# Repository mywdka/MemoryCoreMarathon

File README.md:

# MemoryCoreMarathon
UNRAVEL THE CODE IV, Memory Core Marathon

# Weaving, Driving, Dreaming

Based on the Memory Core Shield from B. North and O. Nash.
Slight routing modifications done to the driver layout, silkscreen and Arduino API.

WdKA API for Unravel the code can be found in the code/ folder.

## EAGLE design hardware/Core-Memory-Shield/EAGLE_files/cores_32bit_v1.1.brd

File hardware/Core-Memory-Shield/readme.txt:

More details of this project can be found at:

    http://www.corememoryshield.com/

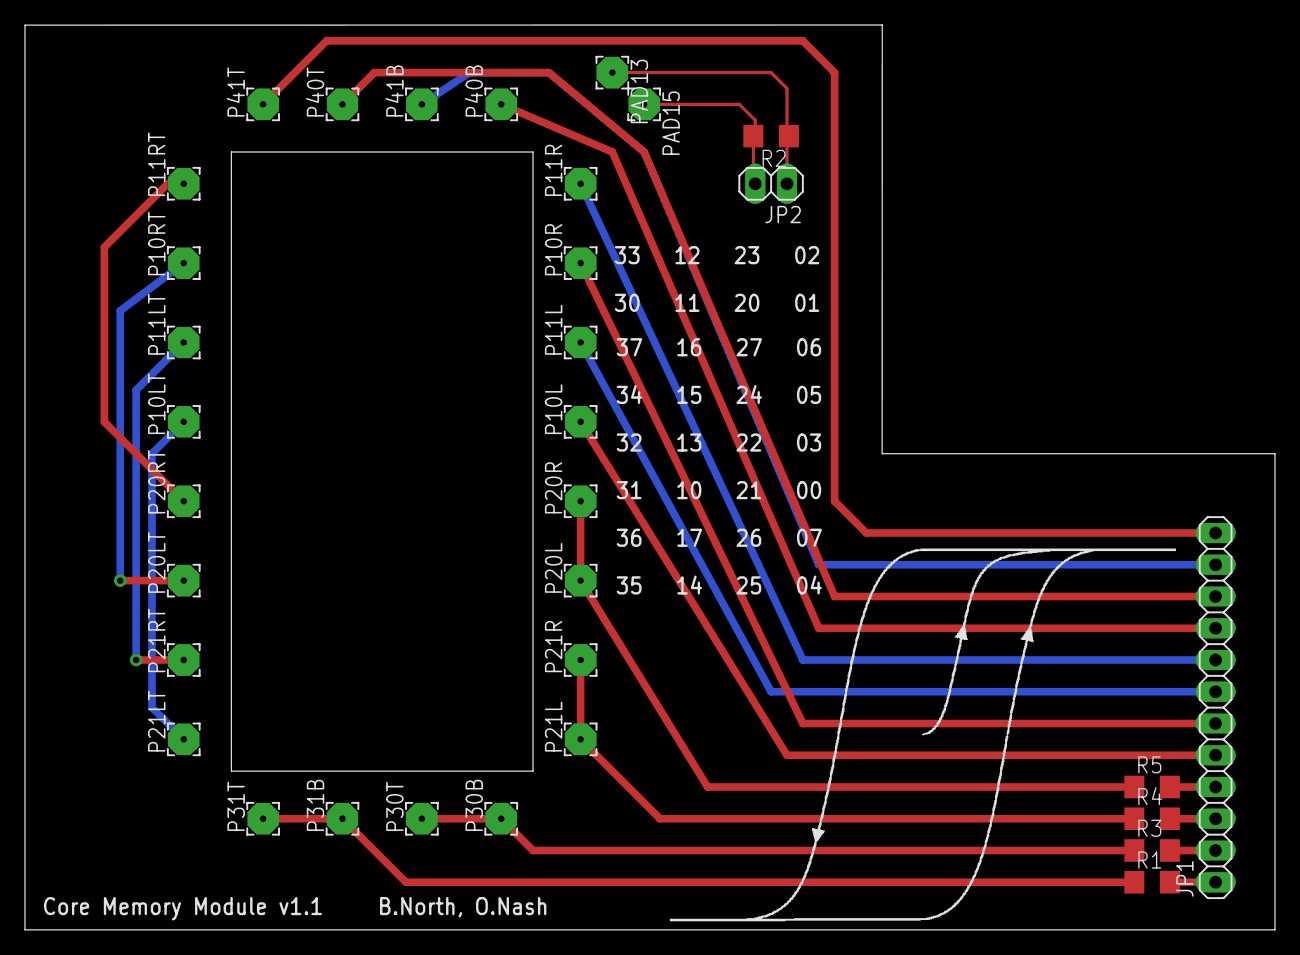
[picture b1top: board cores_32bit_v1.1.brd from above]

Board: 2 copper layers, 100.0 x 72.4 mm, 33 parts (0 on the bottom side), 22 nets.

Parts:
JP1: DRIVER BOARD; 1X12
JP2: SENSE; 1X02
P10L, P10LT, P10R, P10RT, P11L, P11LT, P11R, P11RT, P20L, P20LT, P20R, P20RT, P21L, P21LT, P21R, P21RT, P30B, P30T, P31B, P31T, P40B, P40T, P41B, P41T: WIREPAD2,54/1,1; 2,54/1,1
PAD13, PAD15: WIREPAD2,54/1,1; 2,54/1,1
R1, R3, R4, R5: 18; R1206
R2: 220; R1206

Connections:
D10A: JP1.5, P10L.1
D10B: JP1.6, P10R.1
D11A: JP1.7, P11L.1
D11B: JP1.8, P11R.1
D20: P20L.1, P20R.1, R5.1
D21: P21L.1, P21R.1, R4.1
D30: P30B.1, P30T.1, R3.1
D31: P31B.1, P31T.1, R1.1
D40A: JP1.9, P40B.1
D40B: JP1.10, P40T.1
D41A: JP1.11, P41B.1
D41B: JP1.12, P41T.1
unnamed: JP2.1, PAD13.1, R2.1
unnamed: JP2.2, PAD15.1, R2.2
unnamed: JP1.1, R1.2
unnamed: JP1.2, R3.2
unnamed: JP1.3, R4.2
unnamed: JP1.4, R5.2
unnamed: P10LT.1, P21LT.1
unnamed: P11LT.1, P21RT.1
unnamed: P10RT.1, P20LT.1
unnamed: P11RT.1, P20RT.1

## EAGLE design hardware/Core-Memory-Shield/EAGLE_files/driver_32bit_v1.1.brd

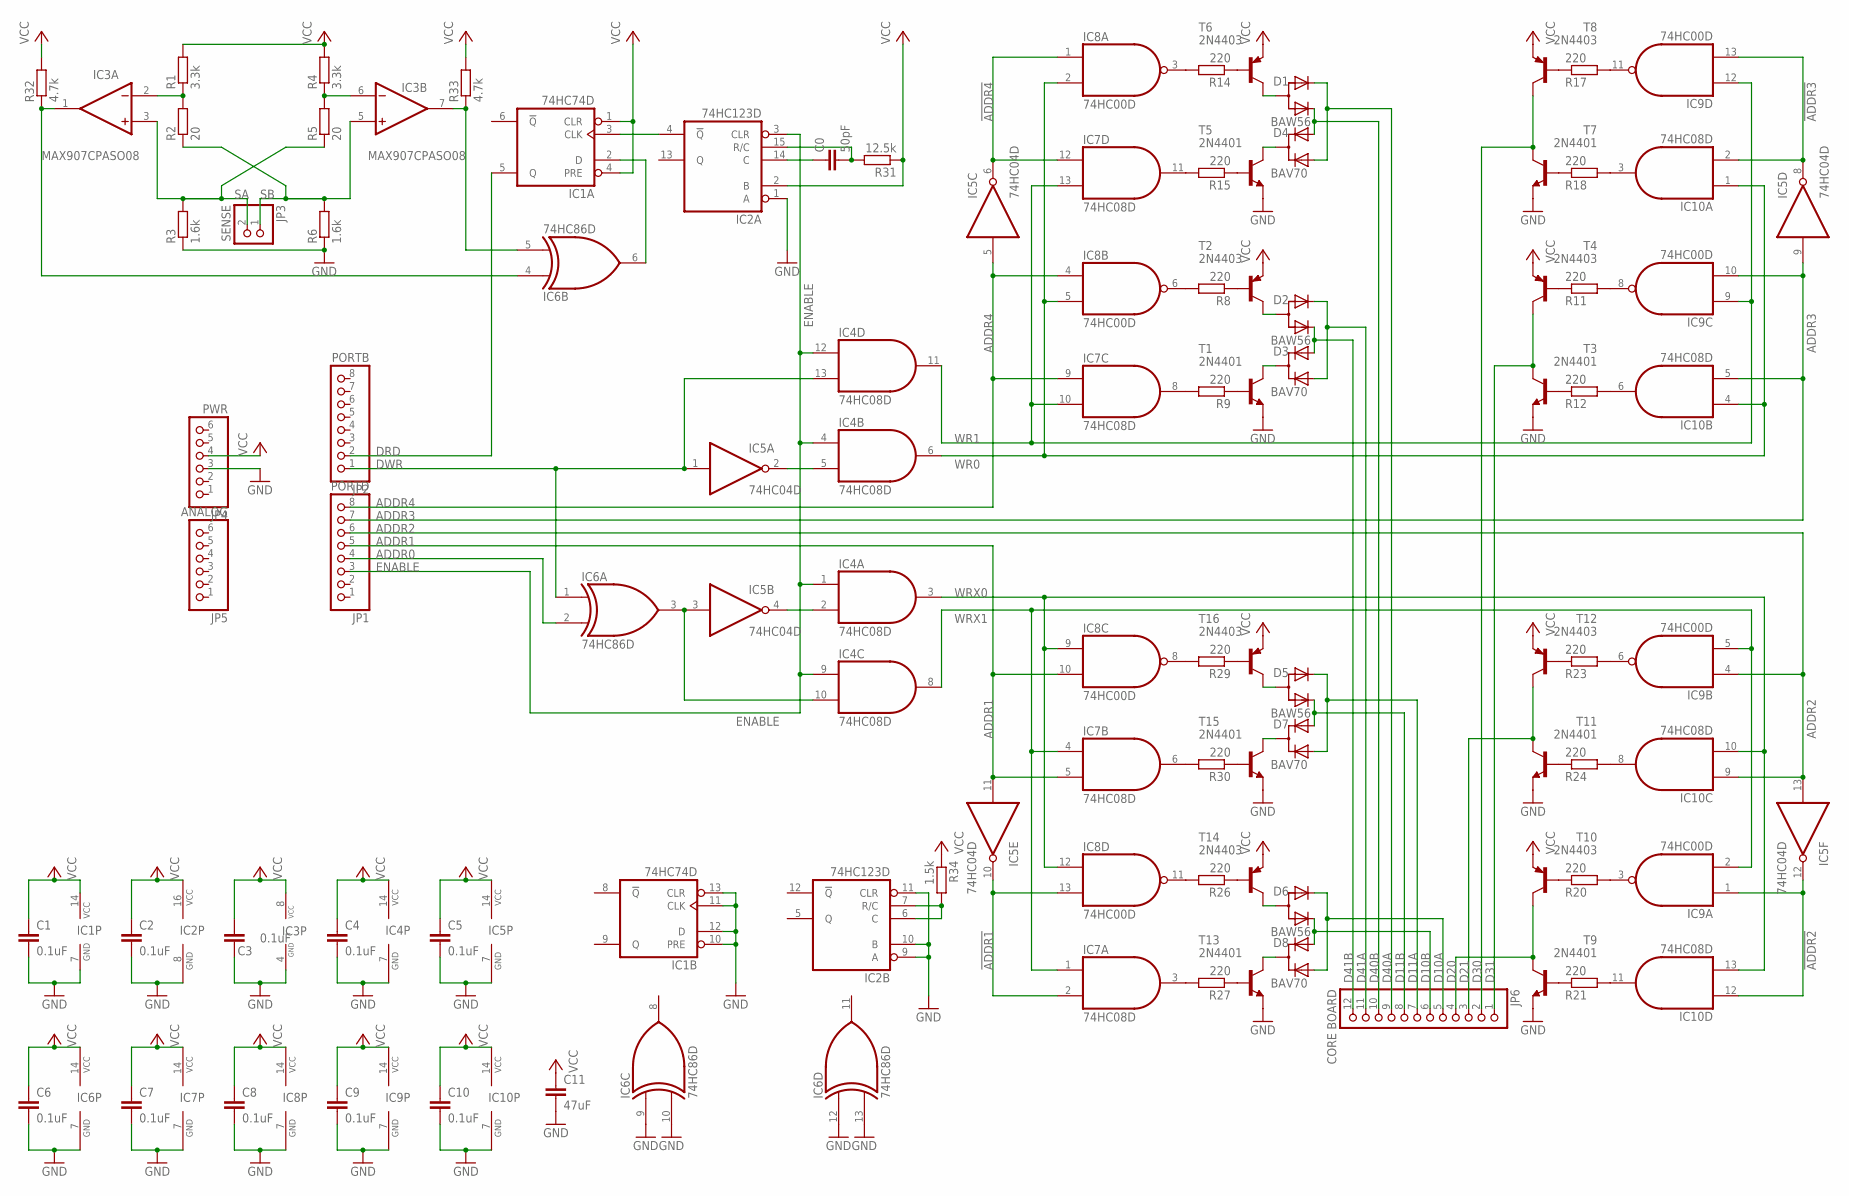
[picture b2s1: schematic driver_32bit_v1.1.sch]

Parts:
C0: 50pF; C1206
C1, C2, C3, C4, C5, C6, C7, C8, C9, C10: 0.1uF; C1206
C11: 47uF; C1206
D1, D2, D5, D6: BAW56; SOT23; MPN BAW56
D3, D4, D7, D8: BAV70; SOT23; MPN BAV70
IC1: 74HC74D; SO14; MPN SN74HC74D
IC2: 74HC123D; SO16; MPN 74HC123D
IC3: MAX907CPASO08; SO08
IC4, IC7, IC10: 74HC08D; SO14; MPN SN74HC08D
IC5: 74HC04D; SO14; MPN SN74HC04D
IC6: 74HC86D; SO14; MPN 74HC86D
IC8, IC9: 74HC00D; SO14; MPN 74HC00D-Q100,118
JP1: PORTD; 1X08
JP2: PORTB; 1X08
JP3: SENSE; 1X02
JP4: PWR; 1X06
JP5: ANALOG; 1X06
JP6: CORE BOARD; 1X12
R1, R4: 3.3k; R1206
R2, R5: 20; R1206
R3, R6: 1.6k; R1206
R8, R9, R11, R12, R14, R15, R17, R18, R20, R21, R23, R24, R26, R27, R29, R30: 220; R1206
R31: 12.5k; R1206
R32, R33: 4.7k; R1206
R34: 1.5k; R1206
T1, T3, T5, T7, T9, T11, T13, T15: 2N4401; SOT23-BEC; MPN 2N4401RLRPG
T2, T4, T6, T8, T10, T12, T14, T16: 2N4403; SOT23-BEC

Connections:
!ADDR1: IC5.10 (O), IC7.2 (I1), IC8.13 (I1)
!ADDR2: IC5.12 (O), IC9.1 (I0), IC10.12 (I0)
!ADDR3: IC5.8 (O), IC9.13 (I1), IC10.2 (I1)
!ADDR4: IC5.6 (O), IC7.12 (I0), IC8.1 (I0)
ADDR0: IC6.2 (I1), JP1.4
ADDR1: IC5.11 (I), IC7.5 (I1), IC8.10 (I1), JP1.5
ADDR2: IC5.13 (I), IC9.4 (I0), IC10.9 (I0), JP1.6
ADDR3: IC5.9 (I), IC9.10 (I1), IC10.5 (I1), JP1.7
ADDR4: IC5.5 (I), IC7.9 (I0), IC8.4 (I0), JP1.8
D10A: D6.1 (K2), D8.2 (A2), JP6.5
D10B: D6.2 (K1), D8.1 (A1), JP6.6
D11A: D5.1 (K2), D7.2 (A2), JP6.7
D11B: D5.2 (K1), D7.1 (A1), JP6.8
D20: JP6.4, T9.C, T10.C
D21: JP6.3, T11.C, T12.C
D30: JP6.2, T7.C, T8.C
D31: JP6.1, T3.C, T4.C
D40A: D1.1 (K2), D4.2 (A2), JP6.9
D40B: D1.2 (K1), D4.1 (A1), JP6.10
D41A: D2.1 (K2), D3.2 (A2), JP6.11
D41B: D2.2 (K1), D3.1 (A1), JP6.12
DRD: IC1.5 (Q), JP2.2
DWR: IC4.13 (I1), IC5.1 (I), IC6.1 (I0), JP2.1
ENABLE: IC2.3 (CLR), IC4.1 (I0), IC4.4 (I0), IC4.9 (I0), IC4.12 (I0), JP1.3
GND: C1.2, C2.2, C3.1, C4.2, C5.2, C6.2, C7.2, C8.2, C9.2, C10.2, C11.2, IC1.7 (GND), IC1.10 (PRE), IC1.11 (CLK), IC1.12 (D), IC1.13 (CLR), IC2.1 (A), IC2.8 (GND), IC2.9 (A), IC2.10 (B), IC2.11 (CLR), IC3.4 (GND), IC4.7 (GND), IC5.7 (GND), IC6.7 (GND), IC6.9 (I0), IC6.10 (I1), IC6.12 (I0), IC6.13 (I1), IC7.7 (GND), IC8.7 (GND), IC9.7 (GND), IC10.7 (GND), JP4.3, R3.1, R6.1, T1.E, T3.E, T5.E, T7.E, T9.E, T11.E, T13.E, T15.E
unnamed: IC3.2 (-IN), R1.1, R2.2
unnamed: IC3.6 (-IN), R4.1, R5.2
unnamed: IC2.6 (C), IC2.7 (R/C), R34.2
unnamed: D1.3 (A), T6.C
unnamed: D2.3 (A), T2.C
unnamed: D5.3 (A), T16.C
unnamed: R8.1, T2.B
unnamed: R9.1, T1.B
unnamed: D3.3 (C), T1.C
unnamed: R11.1, T4.B
unnamed: R12.1, T3.B
unnamed: IC9.11 (O), R17.2
unnamed: IC10.3 (O), R18.2
unnamed: D4.3 (C), T5.C
unnamed: D6.3 (A), T14.C
unnamed: R17.1, T8.B
unnamed: R18.1, T7.B
unnamed: R14.1, T6.B
unnamed: R15.1, T5.B
unnamed: IC7.11 (O), R15.2
unnamed: IC8.3 (O), R14.2
unnamed: IC7.8 (O), R9.2
unnamed: IC8.6 (O), R8.2
unnamed: R20.1, T10.B
unnamed: R21.1, T9.B
unnamed: R23.1, T12.B
unnamed: R24.1, T11.B
unnamed: IC9.3 (O), R20.2
unnamed: IC1.3 (CLK), IC2.4 (!Q)
unnamed: IC1.2 (D), IC6.6 (O)
unnamed: IC3.7 (OUT), IC6.5 (I1), R33.1
unnamed: IC3.1 (OUT), IC6.4 (I0), R32.1
unnamed: C0.1, IC2.14 (C)
unnamed: C0.2, IC2.15 (R/C), R31.2
unnamed: IC4.5 (I1), IC5.2 (O)
unnamed: D7.3 (C), T15.C
unnamed: D8.3 (C), T13.C
unnamed: IC10.11 (O), R21.2
unnamed: IC4.2 (I1), IC5.4 (O)
unnamed: IC4.10 (I1), IC5.3 (I), IC6.3 (O)
unnamed: IC9.8 (O), R11.2
unnamed: R26.1, T14.B
unnamed: IC10.6 (O), R12.2
unnamed: R27.1, T13.B
unnamed: IC9.6 (O), R23.2
unnamed: IC10.8 (O), R24.2
unnamed: R29.1, T16.B
unnamed: R30.1, T15.B
unnamed: IC7.6 (O), R30.2
unnamed: IC8.8 (O), R29.2
unnamed: IC7.3 (O), R27.2
unnamed: IC8.11 (O), R26.2
SA: IC3.3 (+IN), JP3.2, R3.2, R5.1
SB: IC3.5 (+IN), JP3.1, R2.1, R6.2
VCC: C1.1, C2.1, C3.2, C4.1, C5.1, C6.1, C7.1, C8.1, C9.1, C10.1, C11.1, IC1.1 (CLR), IC1.4 (PRE), IC1.14 (VCC), IC2.2 (B), IC2.16 (VCC), IC3.8 (VCC), IC4.14 (VCC), IC5.14 (VCC), IC6.14 (VCC), IC7.14 (VCC), IC8.14 (VCC), IC9.14 (VCC), IC10.14 (VCC), JP4.4, R1.2, R4.2, R31.1, R32.2, R33.2, R34.1, T2.E, T4.E, T6.E, T8.E, T10.E, T12.E, T14.E, T16.E
WR0: IC4.6 (O), IC8.2 (I1), IC8.5 (I1), IC10.1 (I0), IC10.4 (I0)
WR1: IC4.11 (O), IC7.10 (I1), IC7.13 (I1), IC9.9 (I0), IC9.12 (I0)
WRX0: IC4.3 (O), IC8.9 (I0), IC8.12 (I0), IC10.10 (I1), IC10.13 (I1)
WRX1: IC4.8 (O), IC7.1 (I0), IC7.4 (I0), IC9.2 (I1), IC9.5 (I1)

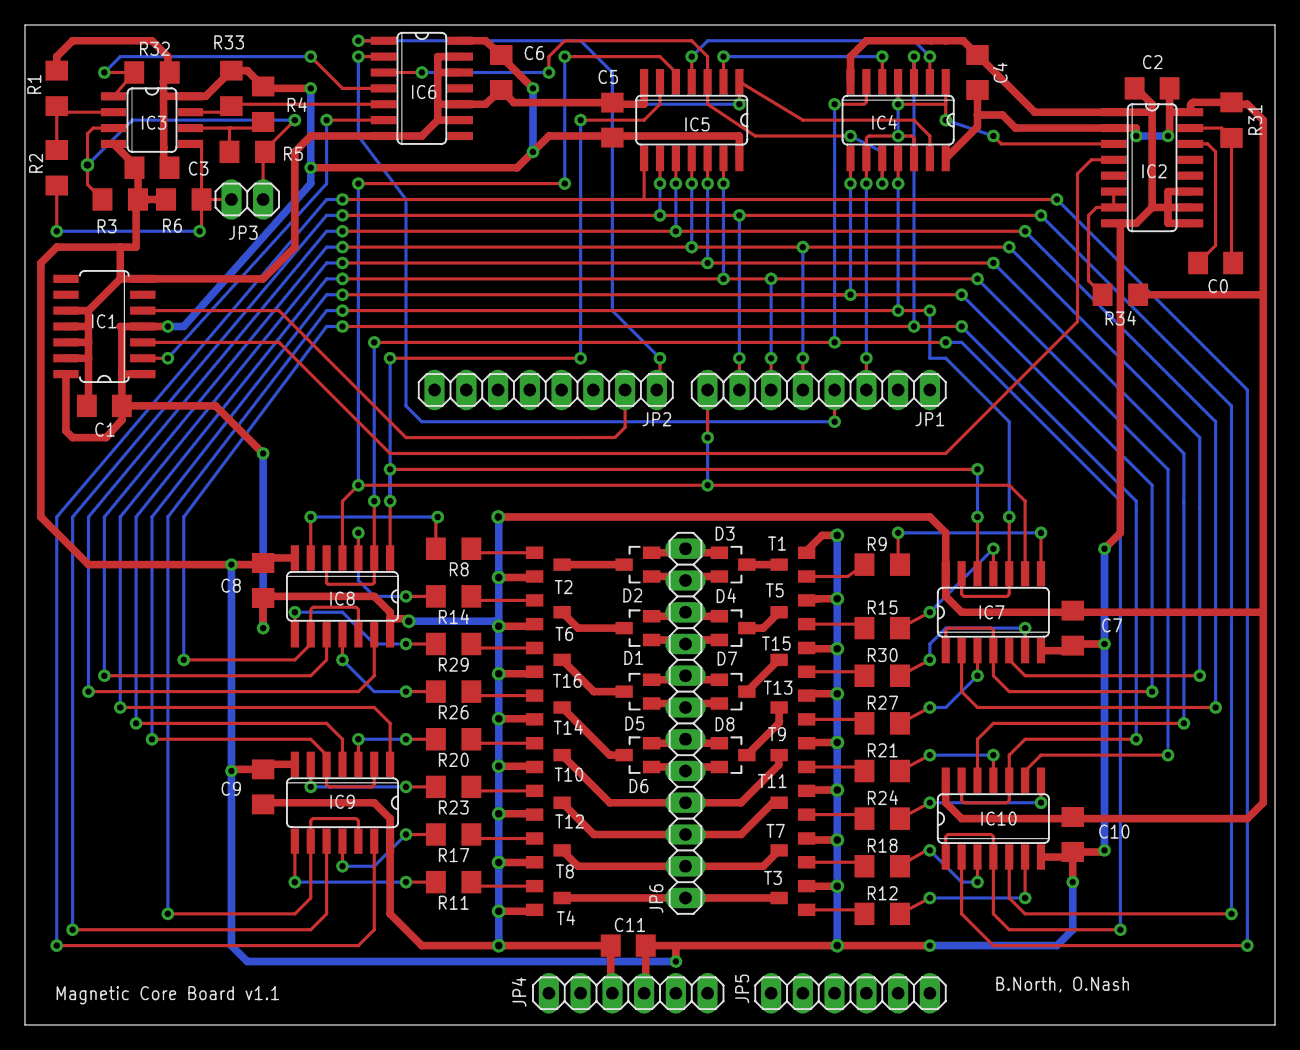
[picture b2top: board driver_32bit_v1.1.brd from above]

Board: 2 copper layers, 100.0 x 80.0 mm, 78 parts (0 on the bottom side), 84 nets.

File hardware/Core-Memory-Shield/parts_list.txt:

Below is the list of necessary parts for building a magnetic core memory
Arduino shield v1.1.  We found all of these parts (including the cores
themselves) easily available on at least one of http://www.ebay.com and
http://www.farnell.com and had our PCBs manufactured by
http://www.eurocircuits.com.

One important note is that the value of the four drive resistors, listed
as 18ohm, may need to be adjusted if the cores used are sufficiently
different to ours.


DRIVING:
8x 2N4401/MMBT4401 transistor (SOT-23 package)
8x 2N4403/MMBT4403 transistor (SOT-23 package)
17x 220ohm 1% resistor (1206 package)
4x 18ohm 1% resistor (1206 package) [May need calibration as described above.]
4x BAW56 diode pair (SOT-23 package)
4x BAV70 diode pair (SOT-23 package)

SENSING:
2x 1.3k 1% resistor (1206 package)
2x 3.3k 1% resistor (1206 package)
2x 20ohm 1% resistor (1206 package)
1x dual MAX907CPAS comparator (SO08 package)
2x 4.7k resistor (1206 package)

LATCHING, TIMING:
1x dual 74HC74D latch (SO14 package)
1x dual 74HC123D timer (SO16 package)
1x 47pF capacitor (1206 package)
1x 12.5k resistor (1206 package)

ADDRESSING:
1x hex 74HC04D (SO14 package)
1x quad 74HC86D (SO14 package)
3x quad 74HC08D (SO14 package)
2x quad 74HC00D (SO14 package)

BYPASS/FILTER CAPS:
10x 0.1uF tantalum capacitor (1206 package)
1x 47uF tantalum capacitor (1206 package)

CONNECTIONS:
2x 0.1" (1x8)-pin header (Arduino stackable)
2x 0.1" (1x6)-pin header (Arduino stackable)
1x 0.1" (1x12)-pin header (male)
1x 0.1" (1x2)-pin header (male)
1x 0.1" (1x12)-pin header (female)
1x 0.1" (1x2)-pin header (female)

PCBs:
1x North-Nash driver board v1.1
1x Laser-cut stencil for driver board v1.1
1x North-Nash core board v1.1
~10g solder paste

CORES:
32x ~1mm hard ferrite cores (with wide hysteresis loop)
Several metres of 0.20mm diameter glazed copper wire.

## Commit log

2015-10-14 Updated comment field of magnet_core_shield.ino
2015-10-14 Modified .gitignore
2015-10-14 Added pdf of cores board
